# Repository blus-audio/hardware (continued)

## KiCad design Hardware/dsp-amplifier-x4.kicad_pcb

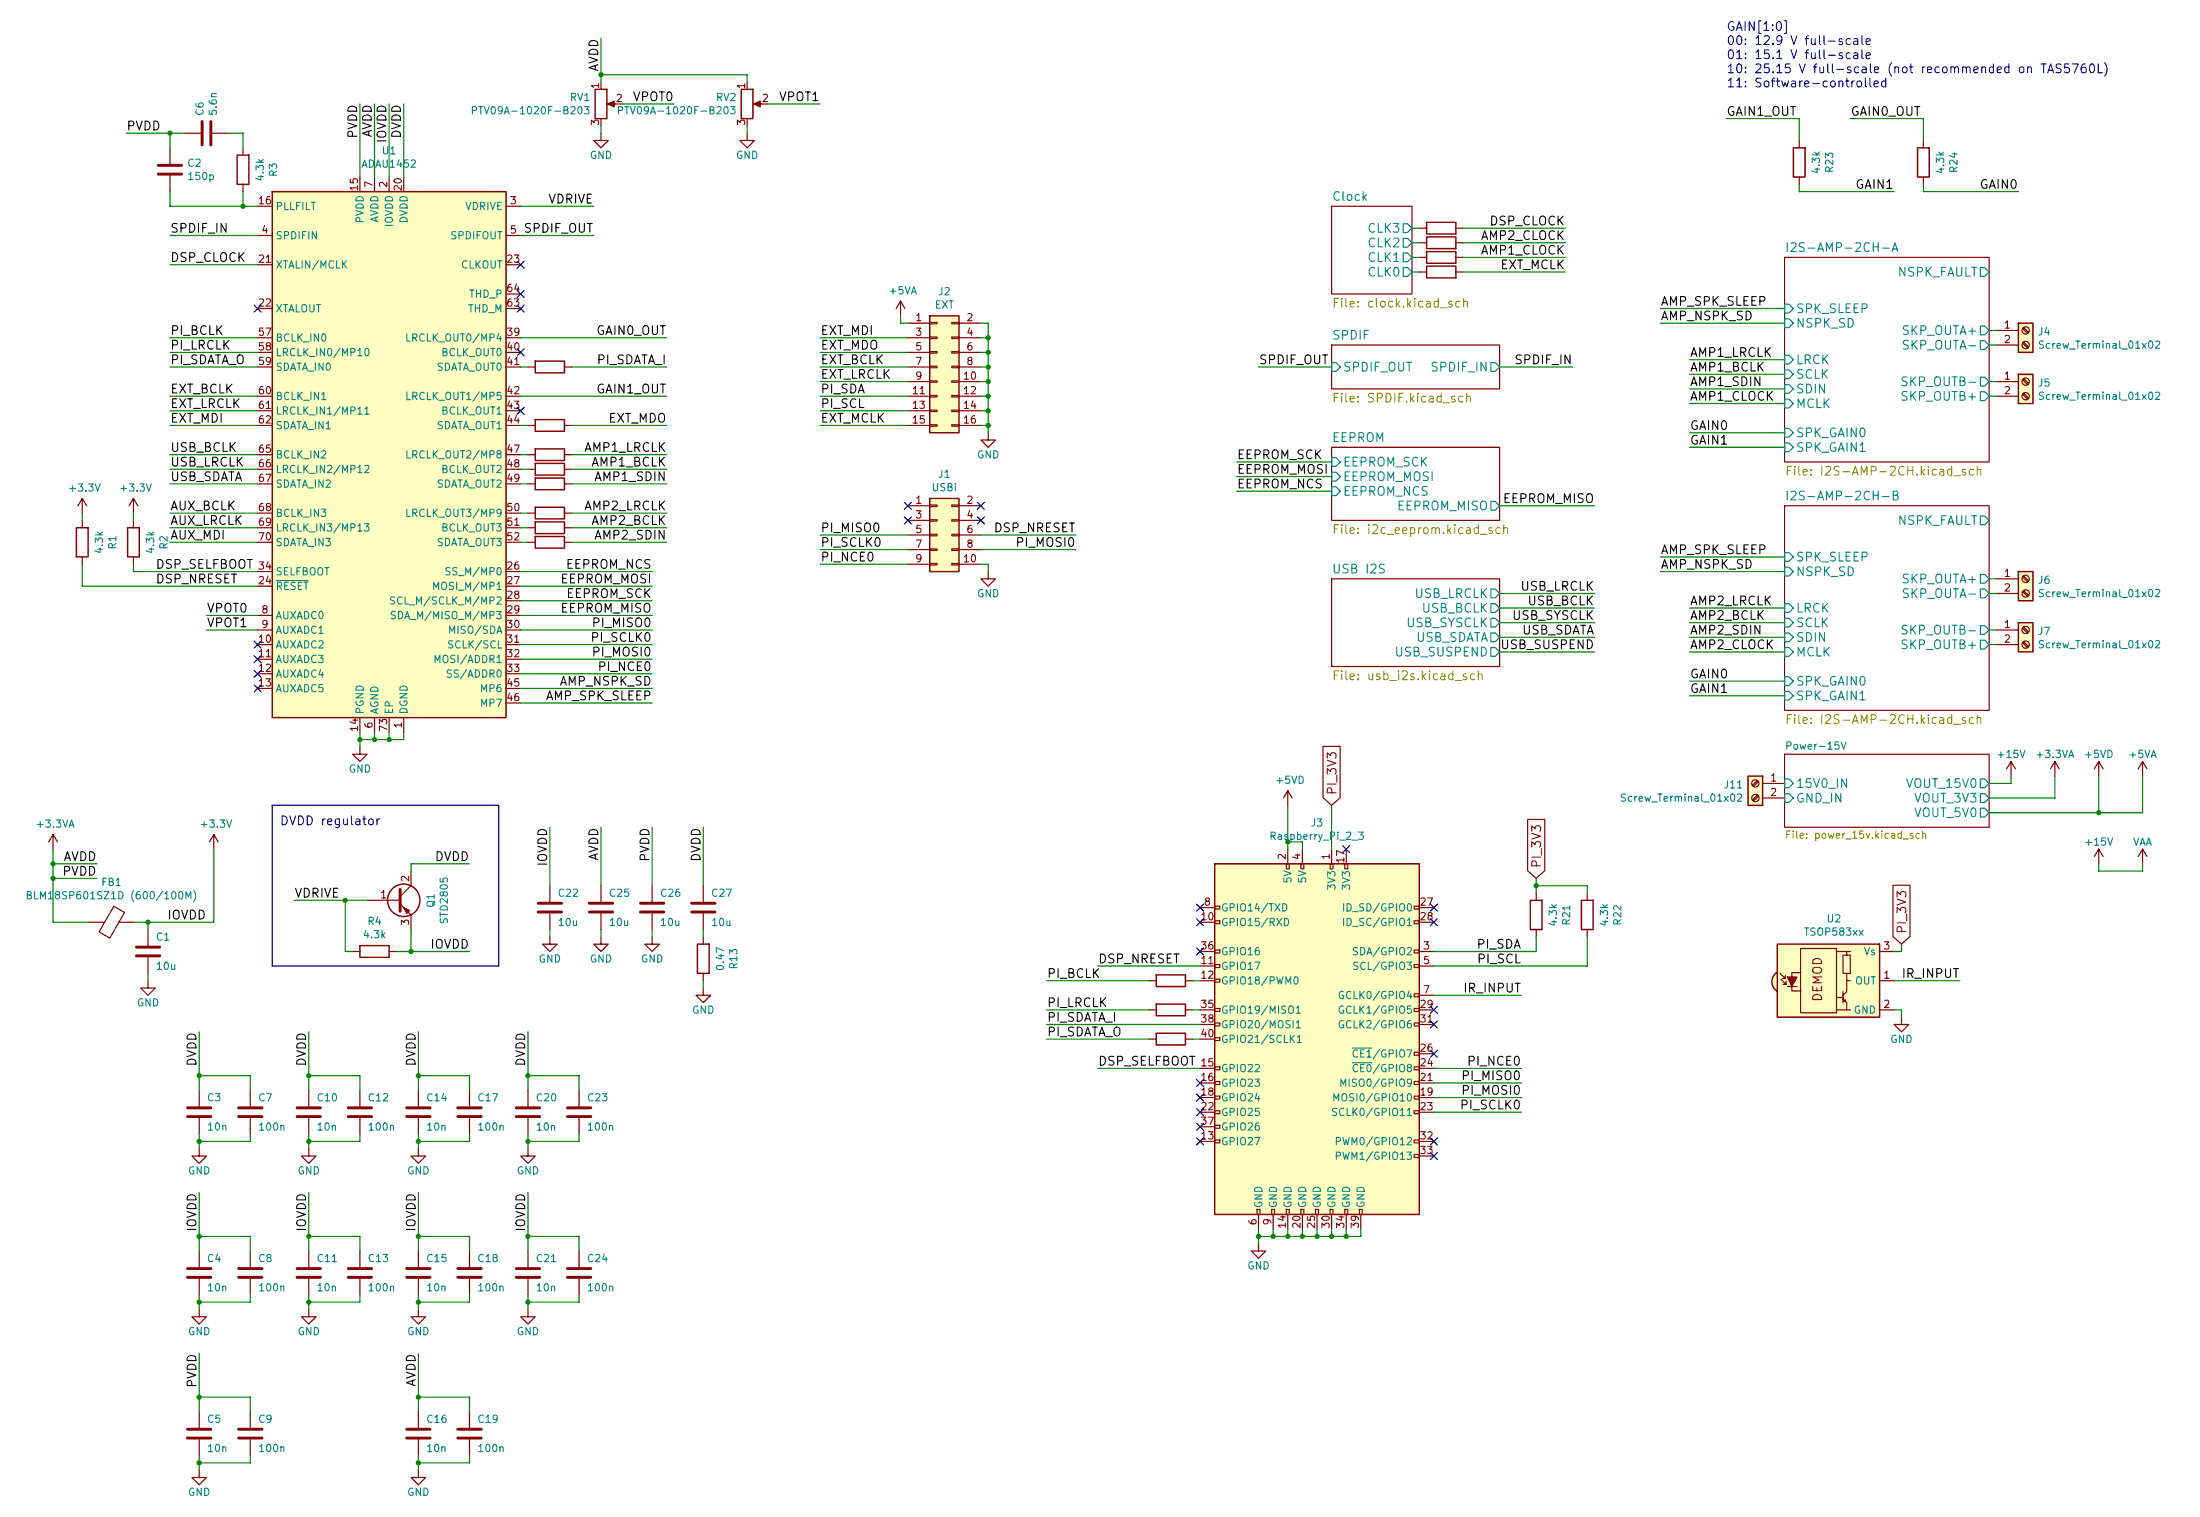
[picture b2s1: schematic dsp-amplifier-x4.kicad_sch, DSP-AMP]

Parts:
C1, C22, C25, C26, C27: 10u; C_1206_3216Metric_Pad1.33x1.80mm_HandSolder
C2: 150p; C_0603_1608Metric_Pad1.08x0.95mm_HandSolder
C3, C4, C5, C10, C11, C14, C15, C16, C20, C21: 10n; C_0603_1608Metric_Pad1.08x0.95mm_HandSolder
C6: 5.6n; C_0603_1608Metric_Pad1.08x0.95mm_HandSolder
C7, C8, C9, C12, C13, C17, C18, C19, C23, C24: 100n; C_0603_1608Metric_Pad1.08x0.95mm_HandSolder
FB1: BLM18SP601SZ1D (600/100M); L_0603_1608Metric_Pad1.05x0.95mm_HandSolder
J1: USBi; IDC-Header_2x05_P2.54mm_Vertical
J2: EXT; IDC-Header_2x08_P2.54mm_Vertical
J3: Raspberry_Pi_2_3; PinSocket_2x20_P2.54mm_Vertical
J4, J5, J6, J7, J11: Screw_Terminal_01x02; wuerth_691216410002
Q1: STD2805; TO-252-3_TabPin2
R1, R2, R3, R4, R21, R22, R23, R24: 4.3k; R_0603_1608Metric_Pad0.98x0.95mm_HandSolder
R5, R6, R7, R8, R9, R10, R11, R12, R14, R15, R16, R17, R18, R19, R20: 33; R_0603_1608Metric_Pad0.98x0.95mm_HandSolder
R13: 0.47; R_0603_1608Metric_Pad0.98x0.95mm_HandSolder
RV1, RV2: PTV09A-1020F-B203; Potentiometer_Bourns_PTV09A-1_Single_Vertical
U1: ADAU1452; LFCSP-72-1EP_10x10mm_P0.5mm_EP5.3x5.3mm
U2: TSOP583xx; Vishay_MINICAST-3Pin

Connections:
+3.3VA: C2.1, C5.1, C6.1, C9.1, C16.1, C19.1, C25.1, C26.1, FB1.2, RV1.1, RV2.1, U1.7 (AVDD), U1.15 (PVDD); also elsewhere on the board
+5VA: J2.1, J3.2 (5V), J3.4 (5V); also elsewhere on the board
+15V: J11.1; also elsewhere on the board
/AMP1_BCLK: R8.1; also elsewhere on the board
/AMP1_CLOCK: R19.2; also elsewhere on the board
/AMP1_LRCLK: R7.1; also elsewhere on the board
/AMP1_SDIN: R9.1; also elsewhere on the board
/AMP2_BCLK: R11.1; also elsewhere on the board
/AMP2_CLOCK: R18.2; also elsewhere on the board
/AMP2_LRCLK: R10.1; also elsewhere on the board
/AMP2_SDIN: R12.1; also elsewhere on the board
/AMP_NSPK_SD: U1.45 (MP6); also elsewhere on the board
/AMP_SPK_SLEEP: U1.46 (MP7); also elsewhere on the board
/AUX_BCLK: U1.68 (BCLK_IN3)
/AUX_LRCLK: U1.69 (LRCLK_IN3/MP13)
/AUX_MDI: U1.70 (SDATA_IN3)
/Clock/CLK0: R20.1; also elsewhere on the board
/Clock/CLK1: R19.1; also elsewhere on the board
/Clock/CLK2: R18.1; also elsewhere on the board
/Clock/CLK3: R17.1; also elsewhere on the board
/DSP_CLOCK: R17.2, U1.21 (XTALIN/MCLK)
/DSP_NRESET: J1.6, J3.11 (GPIO17), R1.1, U1.24 (~RESET)
/DSP_SELFBOOT: J3.15 (GPIO22), R2.1, U1.34 (SELFBOOT)
/DVDD: C3.1, C7.1, C10.1, C12.1, C14.1, C17.1, C20.1, C23.1, C27.1, Q1.2 (C), U1.20 (DVDD), U1.35 (DVDD), U1.53 (DVDD), U1.71 (DVDD)
/EEPROM_MISO: U1.29 (SDA_M/MISO_M/MP3); also elsewhere on the board
/EEPROM_MOSI: U1.27 (MOSI_M/MP1); also elsewhere on the board
/EEPROM_NCS: U1.26 (SS_M/MP0); also elsewhere on the board
/EEPROM_SCK: U1.28 (SCL_M/SCLK_M/MP2); also elsewhere on the board
/EXT_BCLK: J2.7, U1.60 (BCLK_IN1)
/EXT_LRCLK: J2.9, U1.61 (LRCLK_IN1/MP11)
/EXT_MCLK: J2.15, R20.2
/EXT_MDI: J2.3, U1.62 (SDATA_IN1)
/EXT_MDO: J2.5, R6.1
/GAIN0: R24.1; also elsewhere on the board
/GAIN0_OUT: R24.2, U1.39 (LRCLK_OUT0/MP4)
/GAIN1: R23.1; also elsewhere on the board
/GAIN1_OUT: R23.2, U1.42 (LRCLK_OUT1/MP5)
/I2S-AMP-2CH-A/SKP_OUTA+: J4.1; also elsewhere on the board
/I2S-AMP-2CH-A/SKP_OUTA-: J4.2; also elsewhere on the board
/I2S-AMP-2CH-A/SKP_OUTB+: J5.2; also elsewhere on the board
/I2S-AMP-2CH-A/SKP_OUTB-: J5.1; also elsewhere on the board
/I2S-AMP-2CH-B/SKP_OUTA+: J6.1; also elsewhere on the board
/I2S-AMP-2CH-B/SKP_OUTA-: J6.2; also elsewhere on the board
/I2S-AMP-2CH-B/SKP_OUTB+: J7.2; also elsewhere on the board
/I2S-AMP-2CH-B/SKP_OUTB-: J7.1; also elsewhere on the board
/IR_INPUT: J3.7 (GCLK0/GPIO4), U2.1 (OUT)
/PI_BCLK: R14.2, U1.57 (BCLK_IN0)
/PI_LRCLK: R15.2, U1.58 (LRCLK_IN0/MP10)
/PI_MISO0: J1.5, J3.21 (MISO0/GPIO9), U1.30 (MISO/SDA)
/PI_MOSI0: J1.8, J3.19 (MOSI0/GPIO10), U1.32 (MOSI/ADDR1)
/PI_NCE0: J1.9, J3.24 (~CE0/GPIO8), U1.33 (SS/ADDR0)
/PI_SCL: J2.13, J3.5 (SCL/GPIO3), R22.1
/PI_SCLK0: J1.7, J3.23 (SCLK0/GPIO11), U1.31 (SCLK/SCL)
/PI_SDA: J2.11, J3.3 (SDA/GPIO2), R21.1
/PI_SDATA_I: J3.38 (GPIO20/MOSI1), R5.1
/PI_SDATA_O: R16.2, U1.59 (SDATA_IN0)
/SPDIF_IN: U1.4 (SPDIFIN); also elsewhere on the board
/SPDIF_OUT: U1.5 (SPDIFOUT); also elsewhere on the board
/USB_BCLK: U1.65 (BCLK_IN2); also elsewhere on the board
/USB_LRCLK: U1.66 (LRCLK_IN2/MP12); also elsewhere on the board
/USB_SDATA: U1.67 (SDATA_IN2); also elsewhere on the board
/VDRIVE: Q1.1 (B), R4.2, U1.3 (VDRIVE)
/VPOT0: RV1.2, U1.8 (AUXADC0)
/VPOT1: RV2.2, U1.9 (AUXADC1)
GND: C1.2, C3.2, C4.2, C5.2, C7.2, C8.2, C9.2, C10.2, C11.2, C12.2, C13.2, C14.2, C15.2, C16.2, C17.2, C18.2, C19.2, C20.2, C21.2, C22.2, C23.2, C24.2, C25.2, C26.2, J1.10, J2.2, J2.4, J2.6, J2.8, J2.10, J2.12, J2.14, J2.16, J3.6 (GND), J3.9 (GND), J3.14 (GND), J3.20 (GND), J3.25 (GND), J3.30 (GND), J3.34 (GND), J3.39 (GND), J11.2, R13.1, RV1.3, RV2.3, U1.1 (DGND), U1.6 (AGND), U1.14 (PGND), U1.17 (DGND), U1.19 (DGND), U1.25 (DGND), U1.36 (DGND), U1.37 (DGND), U1.54 (DGND), U1.55 (DGND), U1.72 (DGND), U1.73 (EP), U2.2 (GND); also elsewhere on the board
unnamed: C2.2, R3.1, U1.16 (PLLFILT)
unnamed: C6.2, R3.2
unnamed: C27.2, R13.2
unnamed: J3.12 (GPIO18/PWM0), R14.1
unnamed: J3.35 (GPIO19/MISO1), R15.1
unnamed: J3.40 (GPIO21/SCLK1), R16.1
unnamed: R5.2, U1.41 (SDATA_OUT0)
unnamed: R6.2, U1.44 (SDATA_OUT1)
unnamed: R7.2, U1.47 (LRCLK_OUT2/MP8)
unnamed: R8.2, U1.48 (BCLK_OUT2)
unnamed: R9.2, U1.49 (SDATA_OUT2)
unnamed: R10.2, U1.50 (LRCLK_OUT3/MP9)
unnamed: R11.2, U1.51 (BCLK_OUT3)
unnamed: R12.2, U1.52 (SDATA_OUT3)
PI_3V3: J3.1 (3V3), R21.2, R22.2, U2.3 (Vs)

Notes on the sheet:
DVDD regulator
GAIN[1:0] 00: 12.9 V full-scale 01: 15.1 V full-scale 10: 25.15 V full-scale (not recommended on TAS5760L) 11: Software-controlled

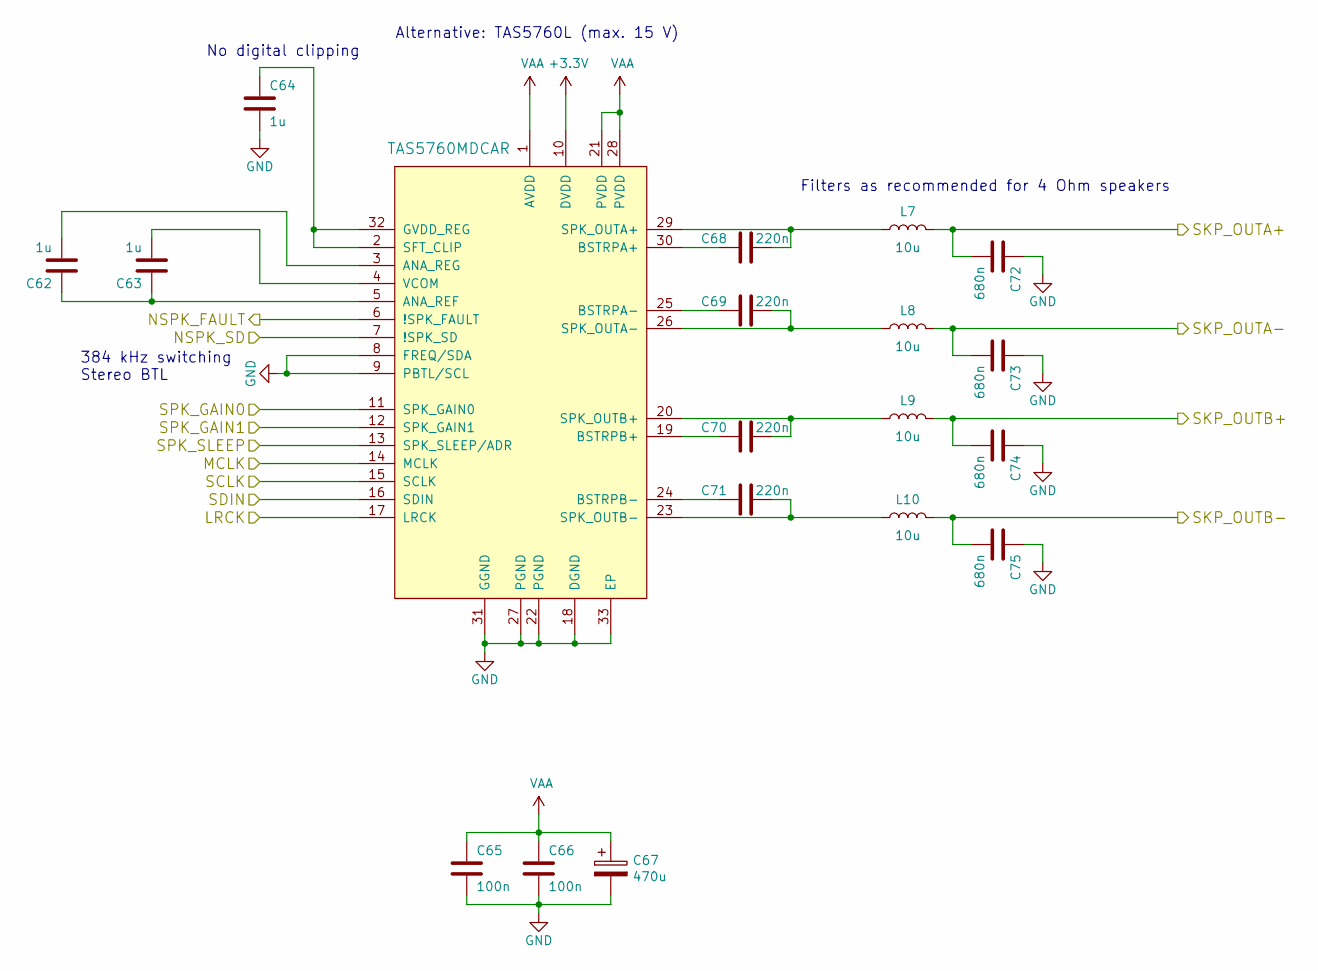
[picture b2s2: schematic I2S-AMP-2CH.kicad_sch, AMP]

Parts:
C62, C63, C64: 1u; C_0805_2012Metric_Pad1.18x1.45mm_HandSolder
C65, C66: 100n; C_0603_1608Metric_Pad1.08x0.95mm_HandSolder
C67: 470u; CP_Radial_D16.0mm_P7.50mm
C68, C69, C70, C71: 220n; C_0603_1608Metric_Pad1.08x0.95mm_HandSolder
C72, C73, C74, C75: 680n; C_0805_2012Metric_Pad1.18x1.45mm_HandSolder
L7, L8, L9, L10: 10u; L_Abracon_ASPI-0630LR
U8: TAS5760MDCAR; HTSSOP-32-1EP_6.1x11mm_P0.65mm_EP5.2x11mm_Mask4.11x4.36mm_T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

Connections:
/AMP2_BCLK: U8.15 (SCLK); also elsewhere on the board
/AMP2_CLOCK: U8.14 (MCLK); also elsewhere on the board
/AMP2_LRCLK: U8.17 (LRCK); also elsewhere on the board
/AMP2_SDIN: U8.16 (SDIN); also elsewhere on the board
/AMP_NSPK_SD: U8.7 (!SPK_SD); also elsewhere on the board
/AMP_SPK_SLEEP: U8.13 (SPK_SLEEP/ADR); also elsewhere on the board
/GAIN0: U8.11 (SPK_GAIN0); also elsewhere on the board
/GAIN1: U8.12 (SPK_GAIN1); also elsewhere on the board
/I2S-AMP-2CH-B/NSPK_FAULT: U8.6 (!SPK_FAULT)
/I2S-AMP-2CH-B/SKP_OUTA+: C72.2, L7.2; also elsewhere on the board
/I2S-AMP-2CH-B/SKP_OUTA-: C73.2, L8.2; also elsewhere on the board
/I2S-AMP-2CH-B/SKP_OUTB+: C74.2, L9.2; also elsewhere on the board
/I2S-AMP-2CH-B/SKP_OUTB-: C75.2, L10.2; also elsewhere on the board
GND: C64.2, C65.2, C66.2, C67.2, C72.1, C73.1, C74.1, C75.1, U8.8 (FREQ/SDA), U8.9 (PBTL/SCL), U8.18 (DGND), U8.22 (PGND), U8.27 (PGND), U8.31 (GGND), U8.33 (EP); also elsewhere on the board
unnamed: C62.1, C63.1, U8.5 (ANA_REF)
unnamed: C62.2, U8.3 (ANA_REG)
unnamed: C63.2, U8.4 (VCOM)
unnamed: C64.1, U8.2 (SFT_CLIP), U8.32 (GVDD_REG)
unnamed: C68.1, U8.30 (BSTRPA+)
unnamed: C68.2, L7.1, U8.29 (SPK_OUTA+)
unnamed: C69.1, U8.25 (BSTRPA-)
unnamed: C69.2, L8.1, U8.26 (SPK_OUTA-)
unnamed: C70.1, U8.19 (BSTRPB+)
unnamed: C70.2, L9.1, U8.20 (SPK_OUTB+)
unnamed: C71.1, U8.24 (BSTRPB-)
unnamed: C71.2, L10.1, U8.23 (SPK_OUTB-)
VAA: C65.1, C66.1, C67.1, U8.1 (AVDD), U8.21 (PVDD), U8.28 (PVDD); also elsewhere on the board

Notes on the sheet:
Filters as recommended for 4 Ohm speakers
No digital clipping
Alternative: TAS5760L (max. 15 V)
384 kHz switching Stereo BTL

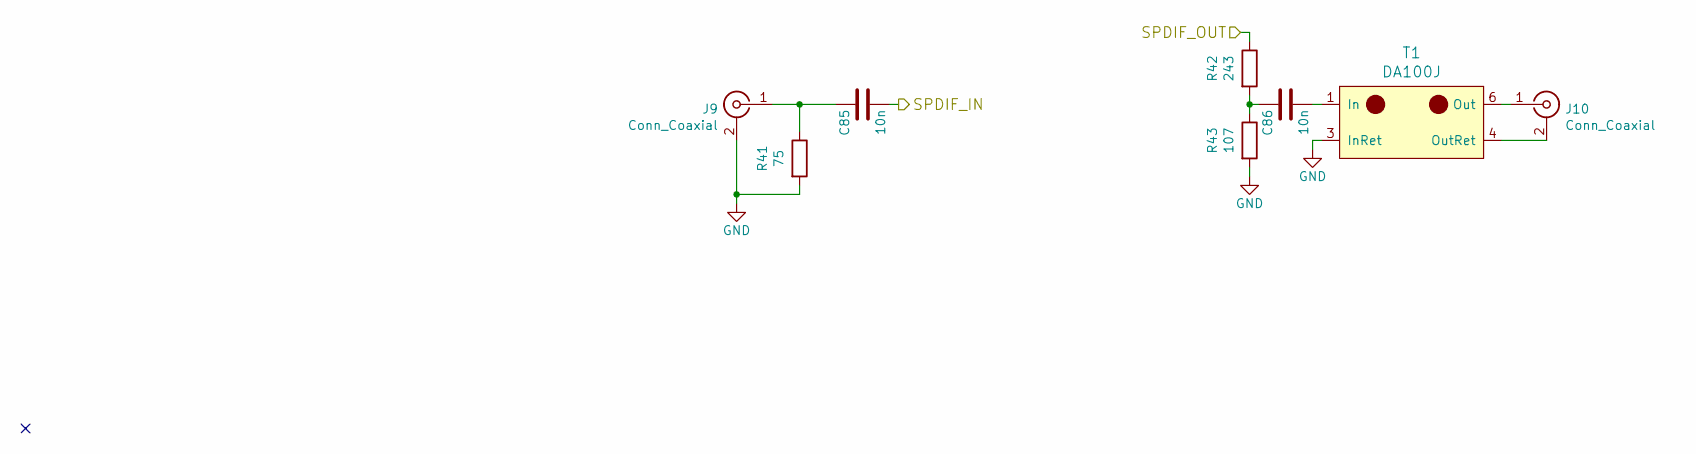
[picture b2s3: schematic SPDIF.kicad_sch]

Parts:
C85, C86: 10n; C_0603_1608Metric_Pad1.08x0.95mm_HandSolder
J9, J10: Conn_Coaxial; cui_rcj_02x
R41: 75; R_0603_1608Metric_Pad0.98x0.95mm_HandSolder
R42: 243; R_0603_1608Metric_Pad0.98x0.95mm_HandSolder
R43: 107; R_0603_1608Metric_Pad0.98x0.95mm_HandSolder
T1: DA100J; SOIC-6

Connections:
/SPDIF_IN: C85.2; also elsewhere on the board
/SPDIF_OUT: R42.1; also elsewhere on the board
GND: J9.2 (Ext), R41.2, R43.2, T1.3 (InRet); also elsewhere on the board
unnamed: C85.1, J9.1 (In), R41.1
unnamed: C86.1, R42.2, R43.1
unnamed: C86.2, T1.1 (In)
unnamed: J10.1 (In), T1.6 (Out)
unnamed: J10.2 (Ext), T1.4 (OutRet)

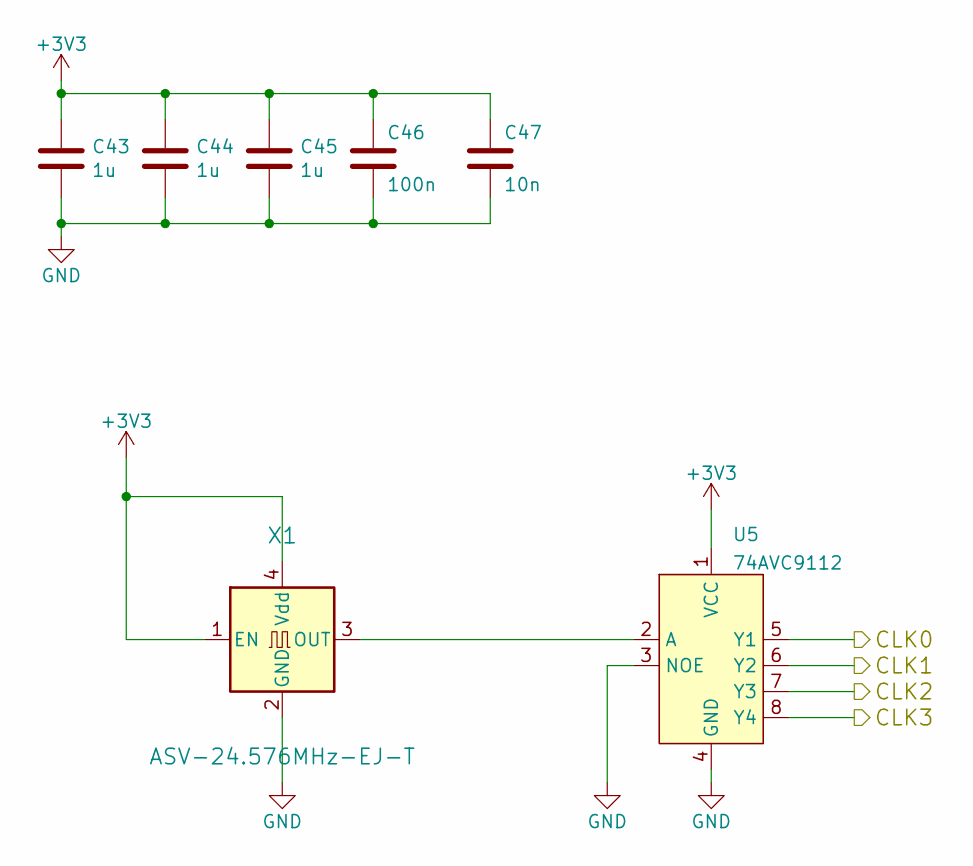
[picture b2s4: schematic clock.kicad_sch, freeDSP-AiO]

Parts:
C43, C44, C45: 1u; C_0805_2012Metric_Pad1.18x1.45mm_HandSolder
C46: 100n; C_0603_1608Metric_Pad1.08x0.95mm_HandSolder
C47: 10n; C_0603_1608Metric_Pad1.08x0.95mm_HandSolder
U5: 74AVC9112; NXP_XSON-8
X1: ASV-24.576MHz-EJ-T; Oscillator_SMD_Abracon_ASV-4Pin_7.0x5.1mm

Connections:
/Clock/CLK0: U5.5 (Y1); also elsewhere on the board
/Clock/CLK1: U5.6 (Y2); also elsewhere on the board
/Clock/CLK2: U5.7 (Y3); also elsewhere on the board
/Clock/CLK3: U5.8 (Y4); also elsewhere on the board
GND: C43.2, C44.2, C45.2, C46.2, C47.2, U5.3 (NOE), U5.4 (GND), X1.2 (GND); also elsewhere on the board
unnamed: U5.2 (A), X1.3 (OUT)

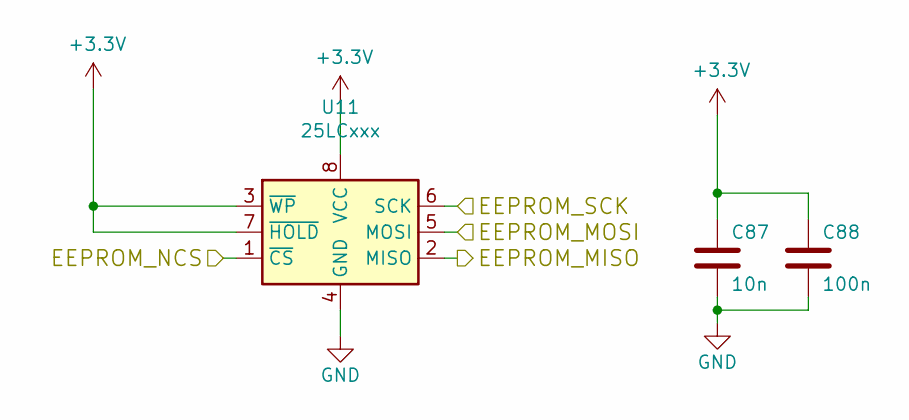
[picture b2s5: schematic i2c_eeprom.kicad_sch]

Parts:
C87: 10n; C_0603_1608Metric_Pad1.08x0.95mm_HandSolder
C88: 100n; C_0603_1608Metric_Pad1.08x0.95mm_HandSolder
U11: 25LCxxx; SOIC-8_5.275x5.275mm_P1.27mm

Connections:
/EEPROM_MISO: U11.2 (MISO); also elsewhere on the board
/EEPROM_MOSI: U11.5 (MOSI); also elsewhere on the board
/EEPROM_NCS: U11.1 (~CS); also elsewhere on the board
/EEPROM_SCK: U11.6 (SCK); also elsewhere on the board
GND: C87.2, C88.2, U11.4 (GND); also elsewhere on the board

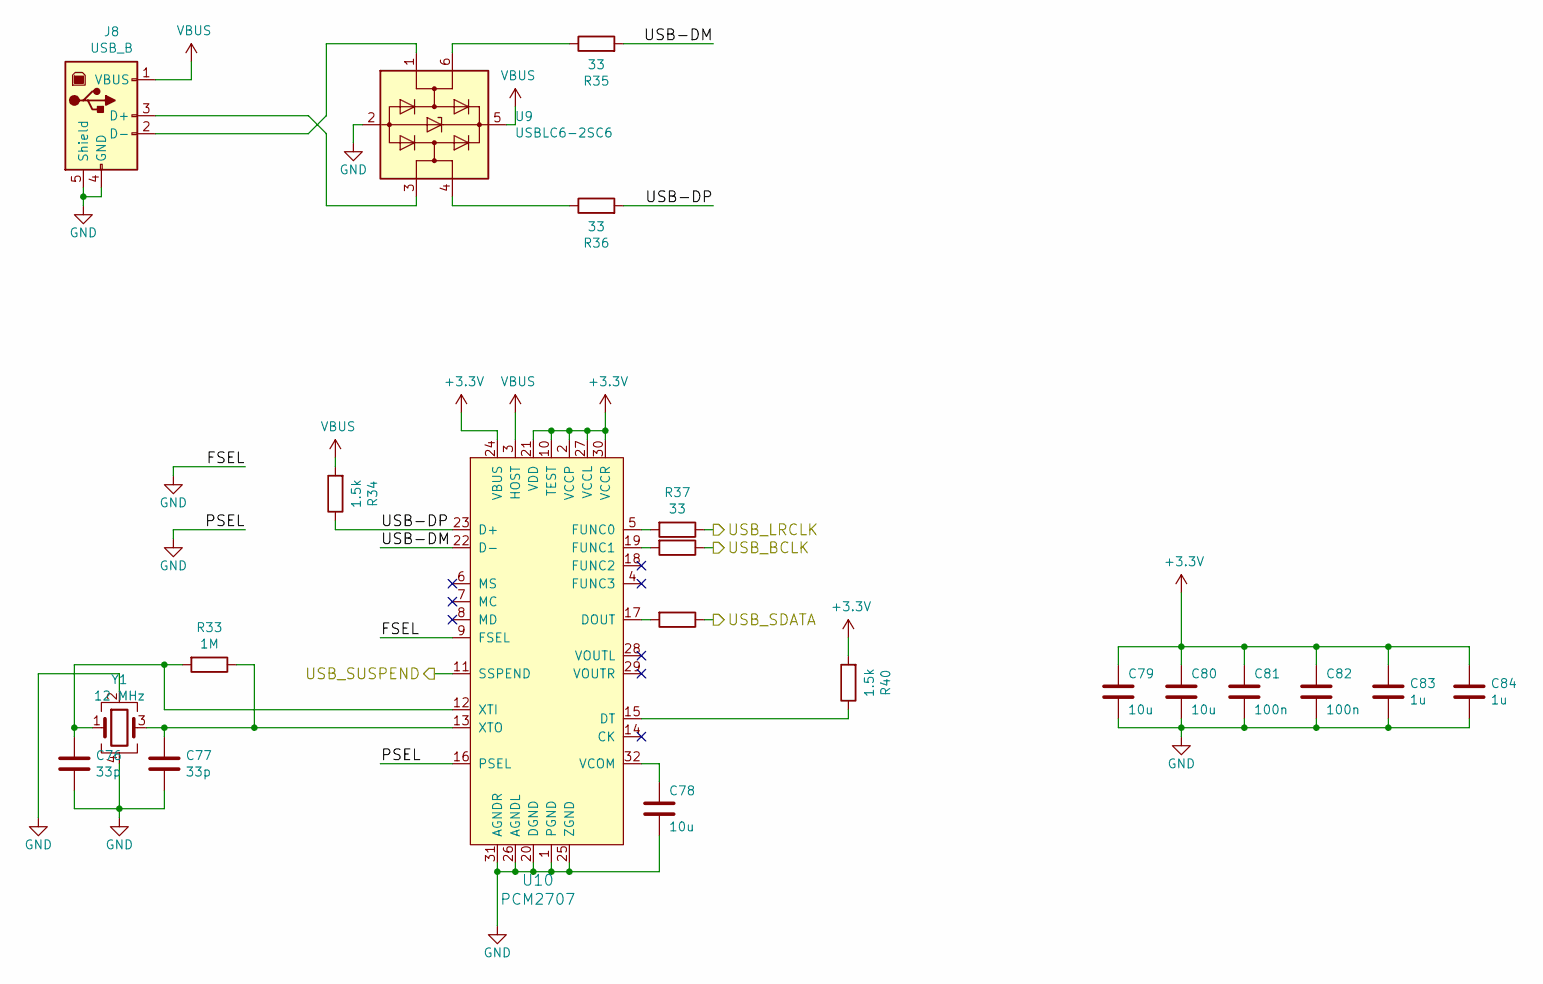
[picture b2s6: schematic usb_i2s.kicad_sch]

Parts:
C76, C77: 33p; C_0603_1608Metric_Pad1.08x0.95mm_HandSolder
C78, C79, C80: 10u; C_1206_3216Metric_Pad1.33x1.80mm_HandSolder
C81, C82: 100n; C_0603_1608Metric_Pad1.08x0.95mm_HandSolder
C83, C84: 1u; C_0805_2012Metric_Pad1.18x1.45mm_HandSolder
J8: USB_B; USB_B_TE_5787834_Vertical
R33: 1M; R_0603_1608Metric_Pad0.98x0.95mm_HandSolder
R34, R40: 1.5k; R_0603_1608Metric_Pad0.98x0.95mm_HandSolder
R35, R36, R37, R38, R39: 33; R_0603_1608Metric_Pad0.98x0.95mm_HandSolder
U9: USBLC6-2SC6; SOT-23-6
U10: PCM2707; TQFP-32_7x7mm_P0.8mm
Y1: 12 MHz; Crystal_SMD_SeikoEpson_FA238-4Pin_3.2x2.5mm

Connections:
/USB I2S/USB-DM: R35.2, U10.22 (D-)
/USB I2S/USB-DP: R34.1, R36.2, U10.23 (D+)
/USB_BCLK: R38.1; also elsewhere on the board
/USB_LRCLK: R37.1; also elsewhere on the board
/USB_SDATA: R39.1; also elsewhere on the board
/USB_SUSPEND: U10.11 (SSPEND)
GND: C76.2, C77.2, C78.2, C79.2, C80.2, C81.2, C82.2, C83.2, C84.2, J8.4 (GND), J8.5 (Shield), U9.2 (GND), U10.1 (PGND), U10.9 (FSEL), U10.16 (PSEL), U10.20 (DGND), U10.25 (ZGND), U10.26 (AGNDL), U10.31 (AGNDR), Y1.2, Y1.4; also elsewhere on the board
unnamed: C76.1, R33.2, U10.12 (XTI), Y1.1
unnamed: C77.1, R33.1, U10.13 (XTO), Y1.3
unnamed: C78.1, U10.32 (VCOM)
unnamed: J8.2 (D-), U9.1 (I/O1)
unnamed: J8.3 (D+), U9.3 (I/O2)
unnamed: R35.1, U9.6 (I/O1)
unnamed: R36.1, U9.4 (I/O2)
unnamed: R37.2, U10.5 (FUNC0)
unnamed: R38.2, U10.19 (FUNC1)
unnamed: R39.2, U10.17 (DOUT)
unnamed: R40.1, U10.15 (DT)
VBUS: J8.1 (VBUS), R34.2, U9.5 (VBUS), U10.3 (HOST)

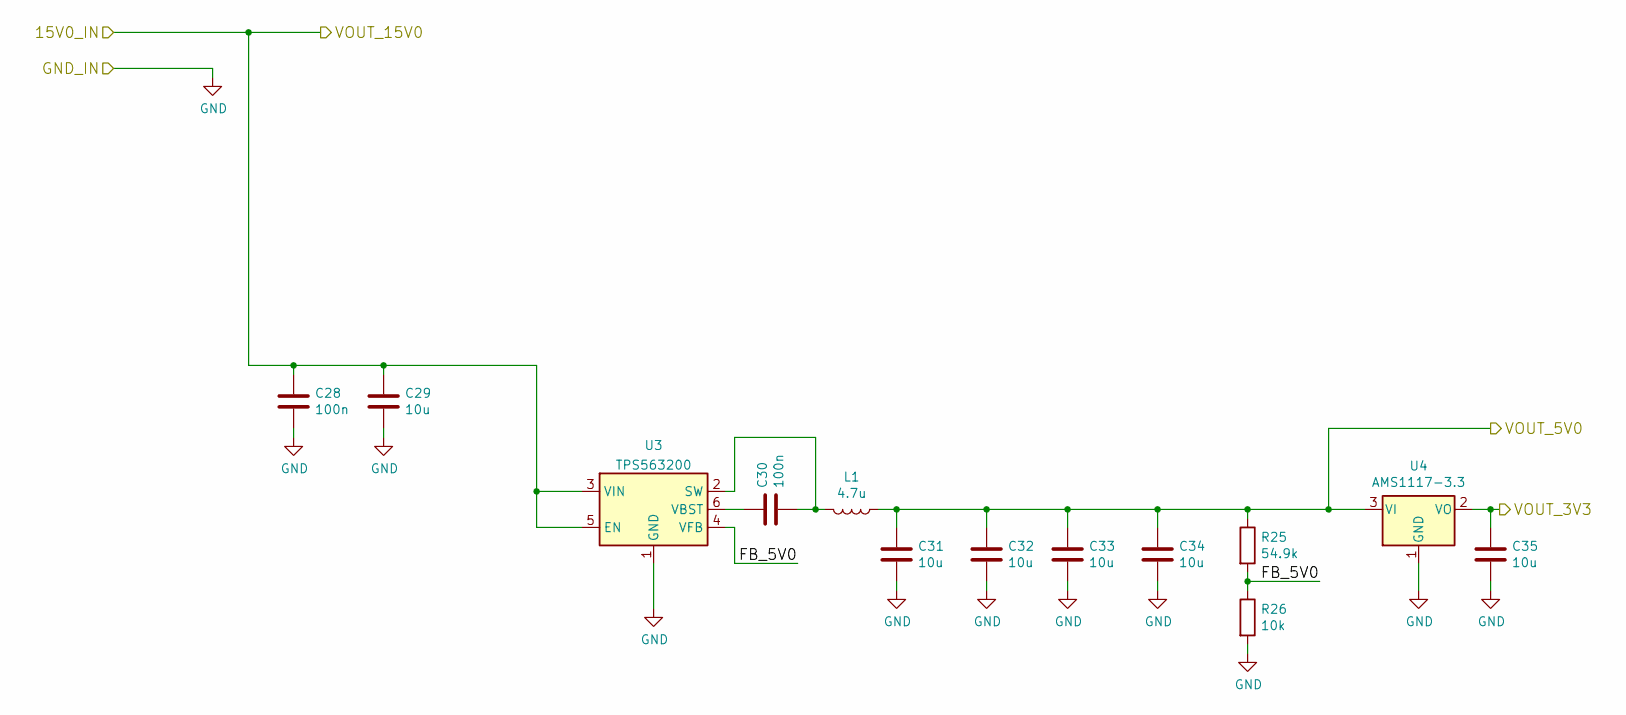
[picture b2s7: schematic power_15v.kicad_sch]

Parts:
C28, C30: 100n; C_0603_1608Metric_Pad1.08x0.95mm_HandSolder
C29, C31, C32, C33, C34, C35: 10u; C_1206_3216Metric_Pad1.33x1.80mm_HandSolder
L1: 4.7u; L_Abracon_ASPI-0630LR
R25: 54.9k; R_0603_1608Metric_Pad0.98x0.95mm_HandSolder
R26: 10k; R_0603_1608Metric_Pad0.98x0.95mm_HandSolder
U3: TPS563200; SOT-23-6
U4: AMS1117-3.3; SOT-223-3_TabPin2

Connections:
+3.3VA: C35.1, U4.2 (VO); also elsewhere on the board
+5VA: C31.1, C32.1, C33.1, C34.1, L1.1, R25.1, U4.3 (VI); also elsewhere on the board
+15V: C28.1, C29.1, U3.3 (VIN), U3.5 (EN); also elsewhere on the board
/Power-15V/FB_5V0: R25.2, R26.1, U3.4 (VFB)
GND: C28.2, C29.2, C31.2, C32.2, C33.2, C34.2, C35.2, R26.2, U3.1 (GND), U4.1 (GND); also elsewhere on the board
unnamed: C30.1, U3.6 (VBST)
unnamed: C30.2, L1.2, U3.2 (SW)

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
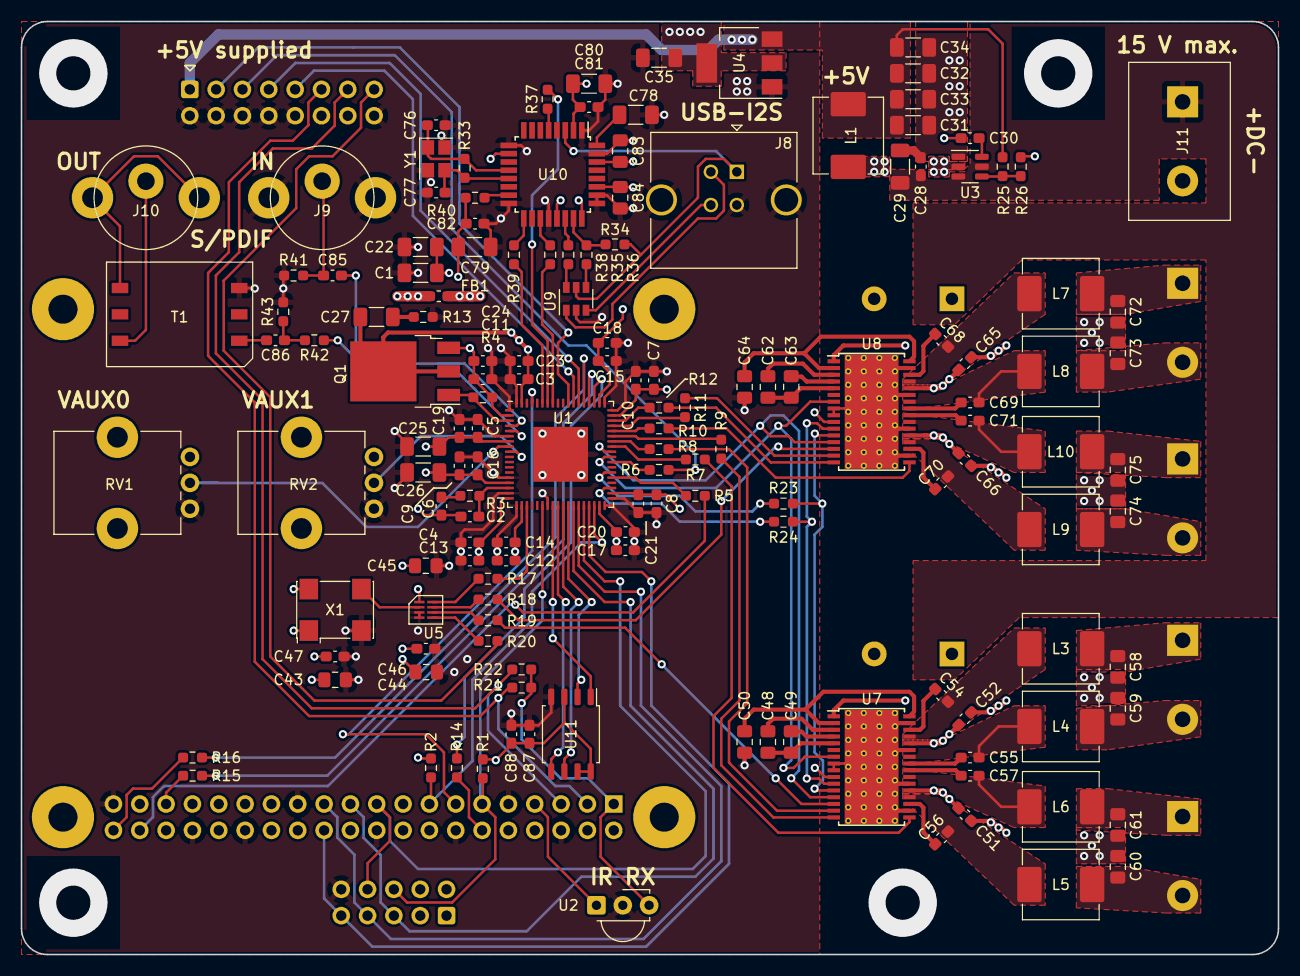
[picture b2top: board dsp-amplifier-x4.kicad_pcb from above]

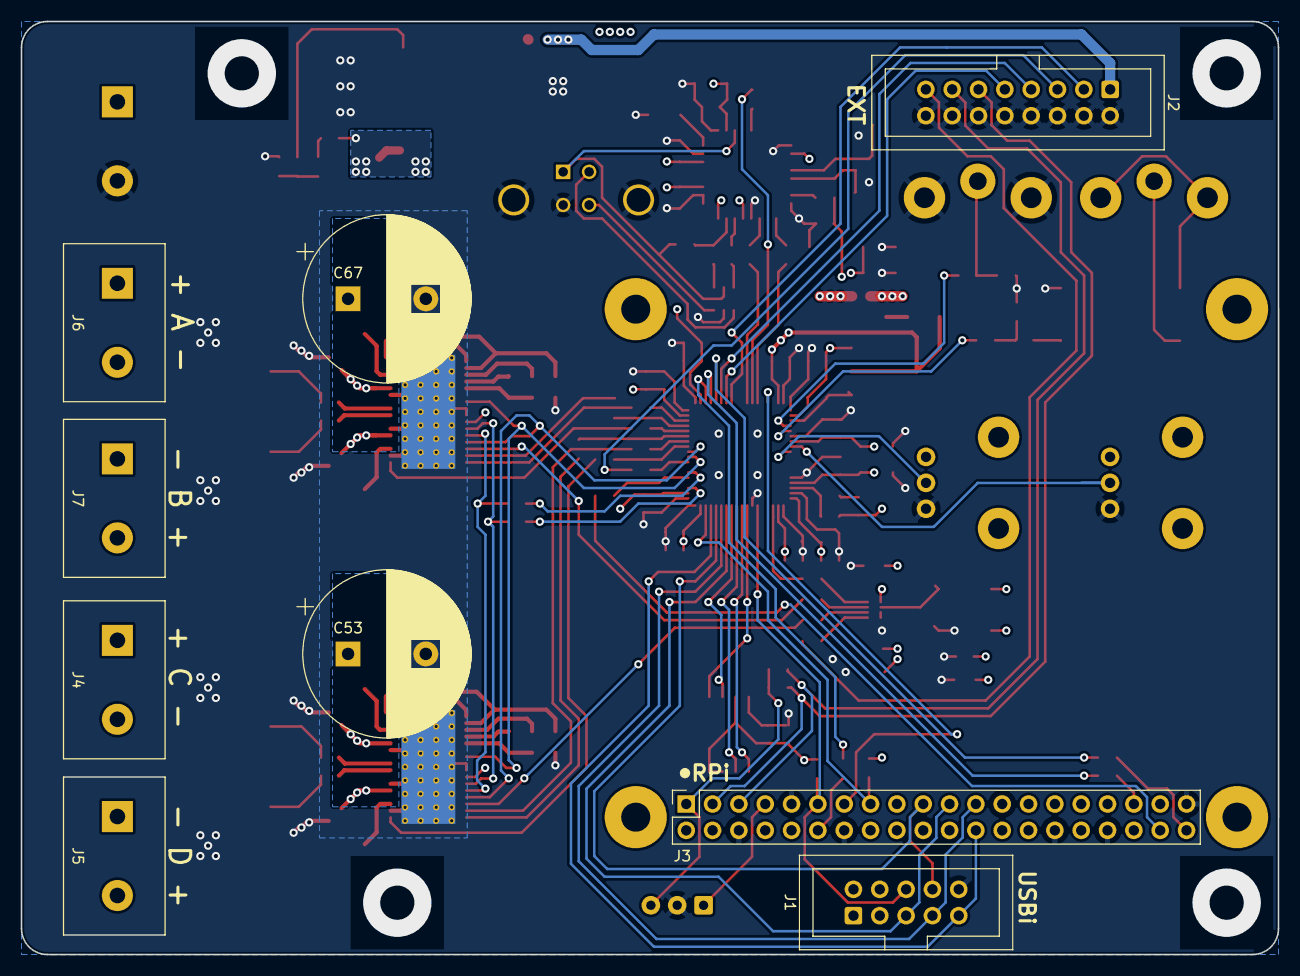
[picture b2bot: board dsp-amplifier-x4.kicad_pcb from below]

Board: 4 copper layers, 121.2 x 90.0 mm, 155 parts (9 on the bottom side), 126 nets.

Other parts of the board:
C48, C49, C50: 1u; C_0805_2012Metric_Pad1.18x1.45mm_HandSolder
C51, C52: 100n; C_0603_1608Metric_Pad1.08x0.95mm_HandSolder
C53: 470u; CP_Radial_D16.0mm_P7.50mm
C54, C55, C56, C57: 220n; C_0603_1608Metric_Pad1.08x0.95mm_HandSolder
C58, C59, C60, C61: 680n; C_0805_2012Metric_Pad1.18x1.45mm_HandSolder
L3, L4, L5, L6: 10u; L_Abracon_ASPI-0630LR
U7: TAS5760MDCAR; HTSSOP-32-1EP_6.1x11mm_P0.65mm_EP5.2x11mm_Mask4.11x4.36mm_T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

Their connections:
/AMP1_BCLK: U7.15 (SCLK); also elsewhere on the board
/AMP1_CLOCK: U7.14 (MCLK); also elsewhere on the board
/AMP1_LRCLK: U7.17 (LRCK); also elsewhere on the board
/AMP1_SDIN: U7.16 (SDIN); also elsewhere on the board
/AMP_NSPK_SD: U7.7 (!SPK_SD); also elsewhere on the board
/AMP_SPK_SLEEP: U7.13 (SPK_SLEEP/ADR); also elsewhere on the board
/GAIN0: U7.11 (SPK_GAIN0); also elsewhere on the board
/GAIN1: U7.12 (SPK_GAIN1); also elsewhere on the board
/I2S-AMP-2CH-A/SKP_OUTA+: C58.2, L3.2; also elsewhere on the board
/I2S-AMP-2CH-A/SKP_OUTA-: C59.2, L4.2; also elsewhere on the board
/I2S-AMP-2CH-A/SKP_OUTB+: C60.2, L5.2; also elsewhere on the board
/I2S-AMP-2CH-A/SKP_OUTB-: C61.2, L6.2; also elsewhere on the board
GND: C50.2, C51.2, C52.2, C53.2, C58.1, C59.1, C60.1, C61.1, U7.8 (FREQ/SDA), U7.9 (PBTL/SCL), U7.18 (DGND), U7.22 (PGND), U7.27 (PGND), U7.31 (GGND), U7.33 (EP); also elsewhere on the board
unnamed: C48.1, C49.1, U7.5 (ANA_REF)
unnamed: C48.2, U7.3 (ANA_REG)
unnamed: C49.2, U7.4 (VCOM)
unnamed: C50.1, U7.2 (SFT_CLIP), U7.32 (GVDD_REG)
unnamed: C54.1, U7.30 (BSTRPA+)
unnamed: C54.2, L3.1, U7.29 (SPK_OUTA+)
unnamed: C55.1, U7.25 (BSTRPA-)
unnamed: C55.2, L4.1, U7.26 (SPK_OUTA-)
unnamed: C56.1, U7.19 (BSTRPB+)
unnamed: C56.2, L5.1, U7.20 (SPK_OUTB+)
unnamed: C57.1, U7.24 (BSTRPB-)
unnamed: C57.2, L6.1, U7.23 (SPK_OUTB-)
VAA: C51.1, C52.1, C53.1, U7.1 (AVDD), U7.21 (PVDD), U7.28 (PVDD); also elsewhere on the board

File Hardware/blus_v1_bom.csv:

ID;Bezeichner;Gehäuse;Stückzahl;Bezeichnung;Anbieter und Referenz;
1;J2;IDC-Header_2x08_P2.54mm_Vertical;1;EXT;;
2;J1;IDC-Header_2x05_P2.54mm_Vertical;1;USBi;;
3;J3;PinSocket_2x20_P2.54mm_Vertical;1;Raspberry_Pi_2_3;;
4;R22,R21,R24,R23,R4,R3,R2,R1;R_0603_1608Metric_Pad0.98x0.95mm_HandSolder;8;4.3k;;
5;C75,C74,C73,C72,C61,C60,C59,C58;C_0805_2012Metric_Pad1.18x1.45mm_HandSolder;8;680n;;
6;RV2,RV1;Potentiometer_Bourns_PTV09A-1_Single_Vertical;2;PTV09A-1020F-B203;;
7;U2;Vishay_MINICAST-3Pin;1;TSOP583xx;;
8;R40,R34;R_0603_1608Metric_Pad0.98x0.95mm_HandSolder;2;1.5k;;
9;R33;R_0603_1608Metric_Pad0.98x0.95mm_HandSolder;1;1M;;
10;P1;wuerth_691216410002;1;Conn_WallPlug;;
11;J7,J6,J5,J4;wuerth_691216410002;4;Screw_Terminal_01x02;;
12;PS1;Converter_ACDC_MeanWell_IRM-60-xx_THT;1;IRM-60-24;;
13;R14,R39,R38,R37,R36,R35,R20,R19,R17,R18,R16,R15,R12,R11,R10,R9,R8,R7,R6,R5;R_0603_1608Metric_Pad0.98x0.95mm_HandSolder;20;33;;
14;U11;SOIC-8_5.275x5.275mm_P1.27mm;1;25LCxxx;25LC1024-I/SM Microchip Technology | Mouser Deutschland;
15;U7,U8;HTSSOP-32-1EP_6.1x11mm_P0.65mm_EP5.2x11mm_Mask4.11x4.36mm_ThermalVias;2;TAS5760MDCAR;TAS5760MDAP Texas Instruments | Mouser Deutschland;
16;C84,C83,C50,C49,C48,C45,C44,C43,C64,C63,C62;C_0805_2012Metric_Pad1.18x1.45mm_HandSolder;11;1u;;
17;C82,C81,C88,C52,C51,C46,C66,C65,C33,C32,C29,C28,C24,C23,C19,C18,C17,C13,C12,C9,C8,C7;C_0603_1608Metric_Pad1.08x0.95mm_HandSolder;22;100n;;
18;C80,C79,C78,C42,C41,C40,C39,C38,C37,C36,C35,C34,C31,C30,C27,C26,C25,C22,C1;C_1206_3216Metric_Pad1.33x1.80mm_HandSolder;19;10u;;
19;C87,C47,C86,C85,C21,C20,C16,C15,C14,C11,C10,C5,C4,C3;C_0603_1608Metric_Pad1.08x0.95mm_HandSolder;14;10n;;
20;Q1;TO-252-3_TabPin2;1;STD2805;;
21;R41;R_0603_1608Metric_Pad0.98x0.95mm_HandSolder;1;75;;
22;C70,C56,C57,C55,C54,C71,C69,C68;C_0603_1608Metric_Pad1.08x0.95mm_HandSolder;8;220n;;
23;X1;Oscillator_SMD_Abracon_ASV-4Pin_7.0x5.1mm;1;ASV-24.576MHz-EJ-T;ASV-24.576MHZ-EJ-T ABRACON | Mouser Deutschland;
24;U6;TSSOP-16_4.4x5mm_P0.65mm;1;SI53365;SI53365-B-GTR Silicon Labs | Mouser Deutschland;
25;L6,L5,L4,L3,L10,L9,L8,L7,L2,L1;L_Abracon_ASPI-0630LR;10;10u;ASPI-0630LR-100M-T15 ABRACON | Mouser Deutschland;
26;C53,C67;CP_Radial_D16.0mm_P7.50mm;2;470u;UPM1V471MHD6AA Nichicon | Mouser Deutschland;
27;J9,J10;cui_rcj_02x;2;Conn_Coaxial;RCJ-021 CUI Devices | Mouser Deutschland;
28;Y1;Crystal_SMD_SeikoEpson_FA238-4Pin_3.2x2.5mm;1;12 MHz;FA-238V 12.0000MA-C5 Epson Timing | Mouser Deutschland;
29;U10;TQFP-32_7x7mm_P0.8mm;1;PCM2707;PCM2707CPJTR Texas Instruments | Mouser Deutschland;
30;U9;SOT-23-6;1;USBLC6-2SC6;USBLC6-2SC6 STMicroelectronics | Mouser Deutschland;
31;U5;SOT-223-3_TabPin2;1;AMS1117-3.3;REG1117-3.3/2K5 Texas Instruments | Mouser Deutschland;
32;U4,U3;SOT-23-6;2;TPS54308;TPS54202HDDCR Texas Instruments | Mouser Deutschland;Alternative TPS54202 (2A)
33;U1;LFCSP-72-1EP_10x10mm_P0.5mm_EP5.3x5.3mm;1;ADAU1452;ADAU1452KCPZ Analog Devices | Mouser Deutschland;
34;T1;SOIC-6;1;DA100J;DA101JC-R Murata Power Solutions | Mouser Deutschland;
35;R43;R_0603_1608Metric_Pad0.98x0.95mm_HandSolder;1;107;;
36;R42;R_0603_1608Metric_Pad0.98x0.95mm_HandSolder;1;243;;
37;R32,R30;R_0603_1608Metric_Pad0.98x0.95mm_HandSolder;2;13.5k;;
38;R31,R29,R28,R26;R_0603_1608Metric_Pad0.98x0.95mm_HandSolder;4;100k;;
39;R27,R25;R_0603_1608Metric_Pad0.98x0.95mm_HandSolder;2;511k;;
40;R13;R_0603_1608Metric_Pad0.98x0.95mm_HandSolder;1;0.47;;
41;J8;USB_B_TE_5787834_Vertical;1;USB_B;5787834-1 TE Connectivity | Mouser Deutschland;
42;FB1;L_0603_1608Metric_Pad1.05x0.95mm_HandSolder;1;BLM18SP601SZ1D (600/100M);;
43;C77,C76;C_0603_1608Metric_Pad1.08x0.95mm_HandSolder;2;33p;;
44;C6;C_0603_1608Metric_Pad1.08x0.95mm_HandSolder;1;5.6n;;
45;C2;C_0603_1608Metric_Pad1.08x0.95mm_HandSolder;1;150p;;
